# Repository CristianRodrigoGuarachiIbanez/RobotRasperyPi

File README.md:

# PiBot Project
The project PiBot was originally developed to learn the use of the PiBot library for python. 
The PiBot library was originally taken from [*here*](https://gitlab.hrz.tu-chemnitz.de/ketf--tu-chemnitz.de/hufa-pibot.git). This will be used to control a RasperyPy-Robot.
In this repository, the code script to drive the a RasperiPy-Robot through the following parkour using the robot library PiBot is included:

For this porpuse, three ultrasonic sensors were used, which were attached and installed to the RasperyPi-Robot. They return the distance to the obstacles in the environment in three different direction: Left, Middel and Right. The sensors were calibrated and carried out with help of the Pibo library. 

# Installation
PiBot and the corresponding operating system (OS) on a micro sd card are needed.
The OS is already prepared for use.

# How to use
To use the PiBot: 
##### 1. Connect a mouse, keyboard and screen
to the corresponding ports of the Raspberry Pi,
##### 2. Connect the powerbank and the 9V battery 
with their corresponding plugs.
Alternatively, you can also connect the USB cable to a normal 5V USB power supply (like a smartphone charger). The minimum power supply of the charger should be 1.8A.
##### 3. Turn the PiBot on
by setting the left switch to "AKKU" and the right switch to "Motor+Not".
##### 4. Wait
until the operating system has booted successfully.

# How to update
To get the latest version of the project files, you have to perform the following steps:

##### 1. Connect to the internet.
First, make sure, that local computer is connected to the internet.
it could be connected to the WLAN via the network button in the upper right corner.

##### 2. Open a terminal.
That oculd be done by clicking on the terminal icon on the upper taskbar or in the menu.

##### 3. Navigate to the hufa-pibot directory.
it could be done by typing 
```bash
cd ~/hufa-pibot
```

##### 4. Update the repository.
By typing
```bash
git pull
```
the latest version of the files will be downloaded from the server.

# Usage of the library
To use the funcionalities of the PiBot, the library files should be included to your project.
This is already done for all provided files. 
Nevertheless here is the example code how to do this:

```python
from pibot import *
display.sample_function("test")
```

### Further information can be found in [01-Python_Tutorial.md](01-Python_Tutorial.md) and [02-PiBot_Programming_Guide.md](02-PiBot_Programming_Guide.md).

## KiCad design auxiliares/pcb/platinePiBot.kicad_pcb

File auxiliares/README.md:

# Readme for the auxiliary files

### boot.py & boot.sh
These files are responsible for the startup and background routine on the
PiBot.
They have to be placed in the /home/<USER> directory.

### ArduinoPins.svg & RaspberryPins.svg
Here you can find a graphic overview of the used pins on the boards.
The files should be opened with an external viewer.

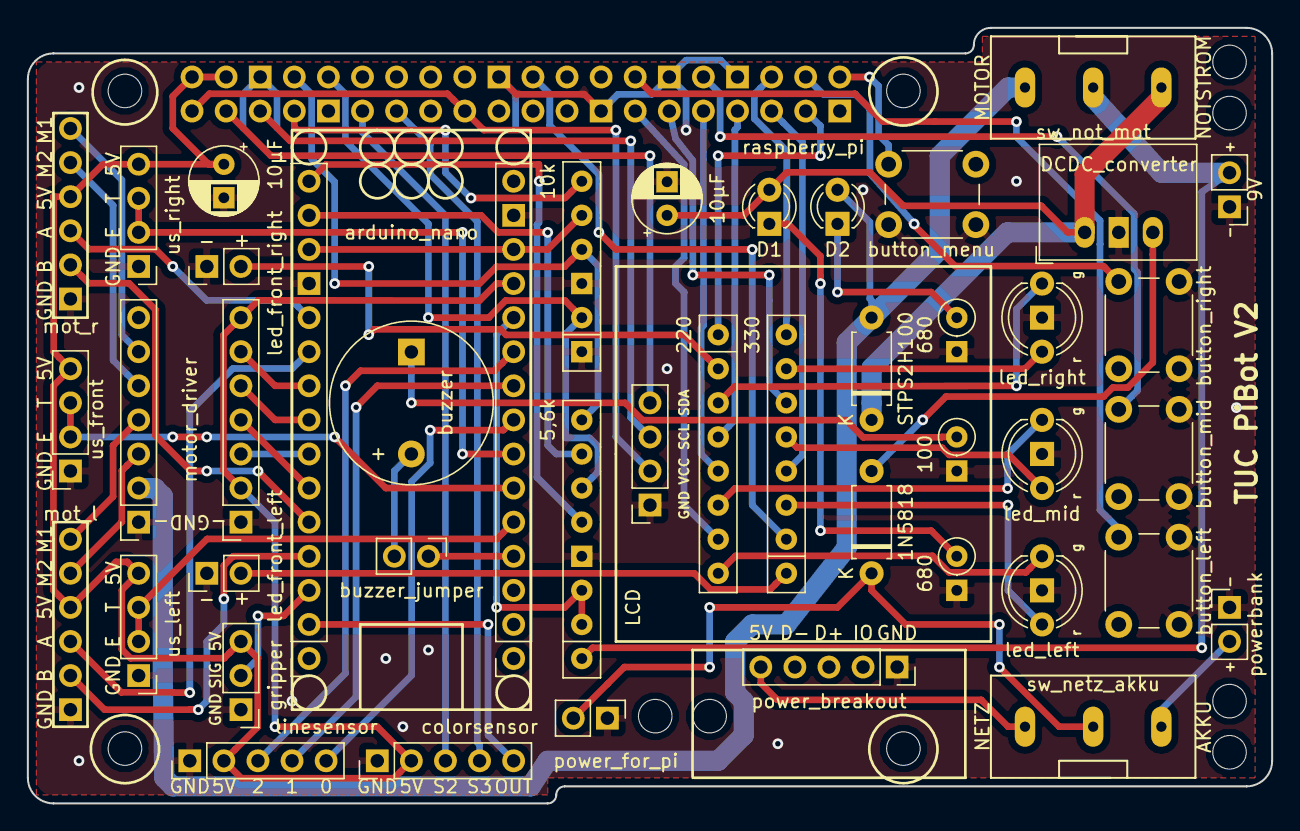
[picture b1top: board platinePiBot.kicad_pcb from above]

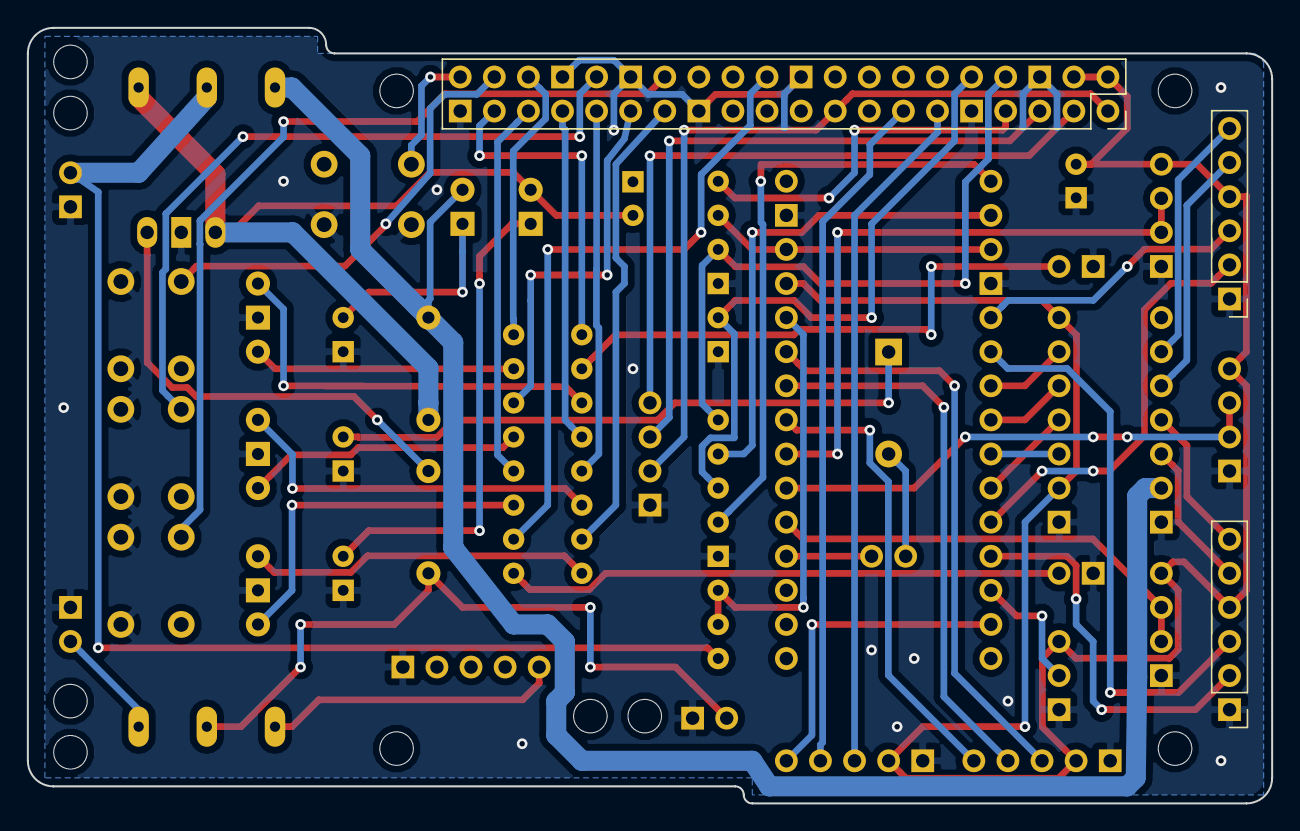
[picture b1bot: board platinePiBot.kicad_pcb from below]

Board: 2 copper layers, 92.7 x 57.8 mm, 55 parts (3 on the bottom side), 66 nets.

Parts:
BZ1: buzzer; Buzzer_12x9.5RM7.6
C1, C2: 10µF; CP_Radial_D5.0mm_P2.50mm
D1: LED_Power_front; LED_D3.0mm
D2: LED_power_rear; LED_D3.0mm
D3: STPS2H100; D_A-405_P7.62mm_Horizontal
D4: led_right; LED_D5.0mm-3
D5: led_mid; LED_D5.0mm-3
D6: led_left; LED_D5.0mm-3
D7: 1N5818; D_A-405_P7.62mm_Horizontal
H1: MountingHole_front_right; MountingHole_2.5mm
H2: MountingHole_front_left; MountingHole_2.5mm
H3: CableHole_side_front; MountingHole_2.5mm
H4: CableHole_side_rear; MountingHole_2.5mm
H6, H6#2, H6#3, H6#4, H6#5, H6#6: CableHole_back_right; MountingHole_2.5mm
J1: mot_r; PinHeader_1x06_P2.54mm_Vertical
J2: us_front; PinSocket_1x04_P2.54mm_Vertical
J3: mot_l; PinHeader_1x06_P2.54mm_Vertical
J4: us_right; PinHeader_1x04_P2.54mm_Vertical
J5: motor_driver; PinSocket_1x07_P2.54mm_Vertical
J6: us_left; PinHeader_1x04_P2.54mm_Vertical
J7: led_front_right; PinHeader_1x02_P2.54mm_Vertical
J8: led_front_left; PinHeader_1x02_P2.54mm_Vertical
J9: Mot_driver_rear; PinSocket_1x07_P2.54mm_Vertical
J10: arduino_nano; PinSocket_1x15_P2.54mm_Vertical
J11: buzzer_jumper; PinHeader_1x02_P2.54mm_Vertical
J12: Nano_rear; PinSocket_1x15_P2.54mm_Vertical
J13: power_for_pi; PinHeader_1x02_P2.54mm_Vertical
J14: LCD; PinSocket_1x04_P2.54mm_Vertical
J15: raspberry_pi; PinSocket_2x20_P2.54mm_Vertical
J16: power_breakout; PinSocket_1x05_P2.54mm_Vertical
J17: colorsensor; PinHeader_1x05_P2.54mm_Vertical
J18: gripper; PinHeader_1x03_P2.54mm_Vertical
J19: linesensor; PinHeader_1x05_P2.54mm_Vertical
J20: powerbank; PinHeader_1x02_P2.54mm_Vertical
J21: 9V; PinHeader_1x02_P2.54mm_Vertical
R7: 100; R_Axial_DIN0207_L6.3mm_D2.5mm_P2.54mm_Vertical
R9, R10: 680; R_Axial_DIN0207_L6.3mm_D2.5mm_P2.54mm_Vertical
RN1: 220; R_Array_SIP8
RN2: 330; R_Array_SIP8
RN3: 10k; R_Array_SIP6
RN4: 5,6k; R_Array_SIP8
SW1: sw_not_mot; switch_tht_3pos
SW2: sw_netz_akku; switch_tht_3pos
SW3: button_mid; SW_PUSH_6mm
SW4: button_left; SW_PUSH_6mm
SW5: button_right; SW_PUSH_6mm
SW6: button_menu; SW_PUSH_6mm
U1: DCDC_converter; Converter_DCDC_RECOM_R-78E-0.5_THT

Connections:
unnamed: BZ1.1, J11.2
unnamed: BZ1.2, R7.1
unnamed: C1.1, J1.4, J2.4, J3.4, J4.4, J6.4, J9.2, J9.7, J12.12, J15.2, J15.4, J17.2, J18.3, J19.2
unnamed: C1.2, C2.2, D4.2, D5.2, D6.2, J1.1, J2.1, J3.1, J4.1, J5.1, J6.1, J7.1, J8.1, J9.1, J10.12, J12.14, J13.1, J14.1, J15.6, J15.9, J15.20, J15.25, J15.30, J15.34, J15.39, J16.1, J17.1, J18.1, J19.1, J20.1, J21.1, R7.2, R9.2, R10.2, RN3.1, RN3.3, RN4.4, SW3.2, SW4.2, SW5.2, SW6.2, U1.2
unnamed: C2.1, D1.2, D3.1, SW1.3, U1.1
unnamed: D1.1, R9.1
unnamed: D2.1, R10.1
unnamed: D2.2, D3.2, J5.2, SW1.1
unnamed: D4.1, RN1.3
unnamed: D4.3, RN2.7
unnamed: D5.1, RN1.6
unnamed: D5.3, RN2.5
unnamed: D6.1, RN1.8
unnamed: D6.3, RN2.3
unnamed: D7.1, J13.2, SW2.2
unnamed: D7.2, U1.3
unnamed: J1.2, J10.5
unnamed: J1.3, J10.11
unnamed: J1.5, J5.5
unnamed: J1.6, J5.6
unnamed: J3.5, J5.3
unnamed: J3.6, J5.4
unnamed: J7.2, RN1.2
unnamed: J8.2, RN2.1
unnamed: J10.2, J17.5
unnamed: J10.3, J18.2
unnamed: J3.2, J10.4
unnamed: J9.4, J10.6
unnamed: J9.3, J10.7
unnamed: J9.5, J10.8
unnamed: J9.6, J10.9
unnamed: J3.3, J10.10
unnamed: J10.13, J12.13, RN3.5
unnamed: J10.14, RN4.7
unnamed: J10.15, RN4.5
unnamed: J11.1, J12.4
unnamed: J6.2, J6.3, J12.5
unnamed: J2.2, J2.3, J12.6
unnamed: J4.2, J4.3, J12.7
unnamed: J12.8, J19.5
unnamed: J12.9, J19.4
unnamed: J12.10, J19.3
unnamed: J12.11, RN4.2, RN4.3
unnamed: J14.2, J15.1, J15.17
unnamed: J14.3, J15.5
unnamed: J14.4, J15.3
unnamed: J15.7, RN3.6
unnamed: J15.8, RN3.4, RN4.8
unnamed: J15.10, RN3.2, RN4.6
unnamed: J15.11, J17.3
unnamed: J15.13, J17.4
unnamed: J15.22, RN2.2
unnamed: J15.27, RN1.7
unnamed: J15.28, SW4.1
unnamed: J15.29, RN2.6
unnamed: J15.31, RN1.5
unnamed: J15.32, SW3.1
unnamed: J15.33, RN1.4
unnamed: J15.35, RN2.4
unnamed: J15.36, RN2.8
unnamed: J15.37, RN1.1
unnamed: J15.38, SW5.1
unnamed: J15.40, SW6.1
unnamed: J16.5, SW2.3
unnamed: J20.2, SW2.1
unnamed: J21.2, RN4.1, SW1.2
